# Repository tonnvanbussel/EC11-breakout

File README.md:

# EC11-breakout
EC11 breakout, article files.

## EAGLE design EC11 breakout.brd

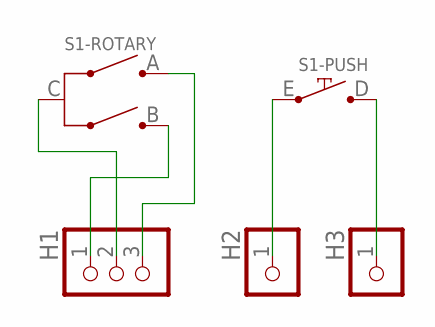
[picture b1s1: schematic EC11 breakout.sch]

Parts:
H1: PINHD-1X03ROUND; 1X03-ROUND
H2, H3: PINHD-1X01ROUND; 1X01-ROUND
S1: EC11

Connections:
unnamed: H1.2, S1.C
unnamed: H2.1, S1.E
unnamed: H1.3, S1.A
unnamed: H1.1, S1.B
unnamed: H3.1, S1.D

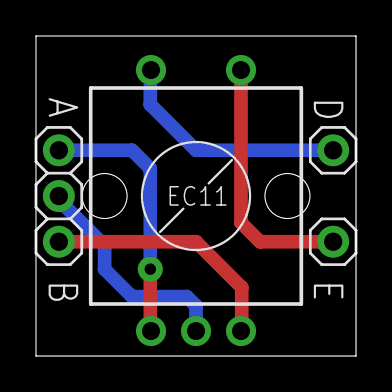
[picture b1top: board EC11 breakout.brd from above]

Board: 2 copper layers, 17.8 x 17.8 mm, 4 parts (0 on the bottom side), 5 nets.

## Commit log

2017-08-29 Files added.
2017-08-29 Create LICENSE
